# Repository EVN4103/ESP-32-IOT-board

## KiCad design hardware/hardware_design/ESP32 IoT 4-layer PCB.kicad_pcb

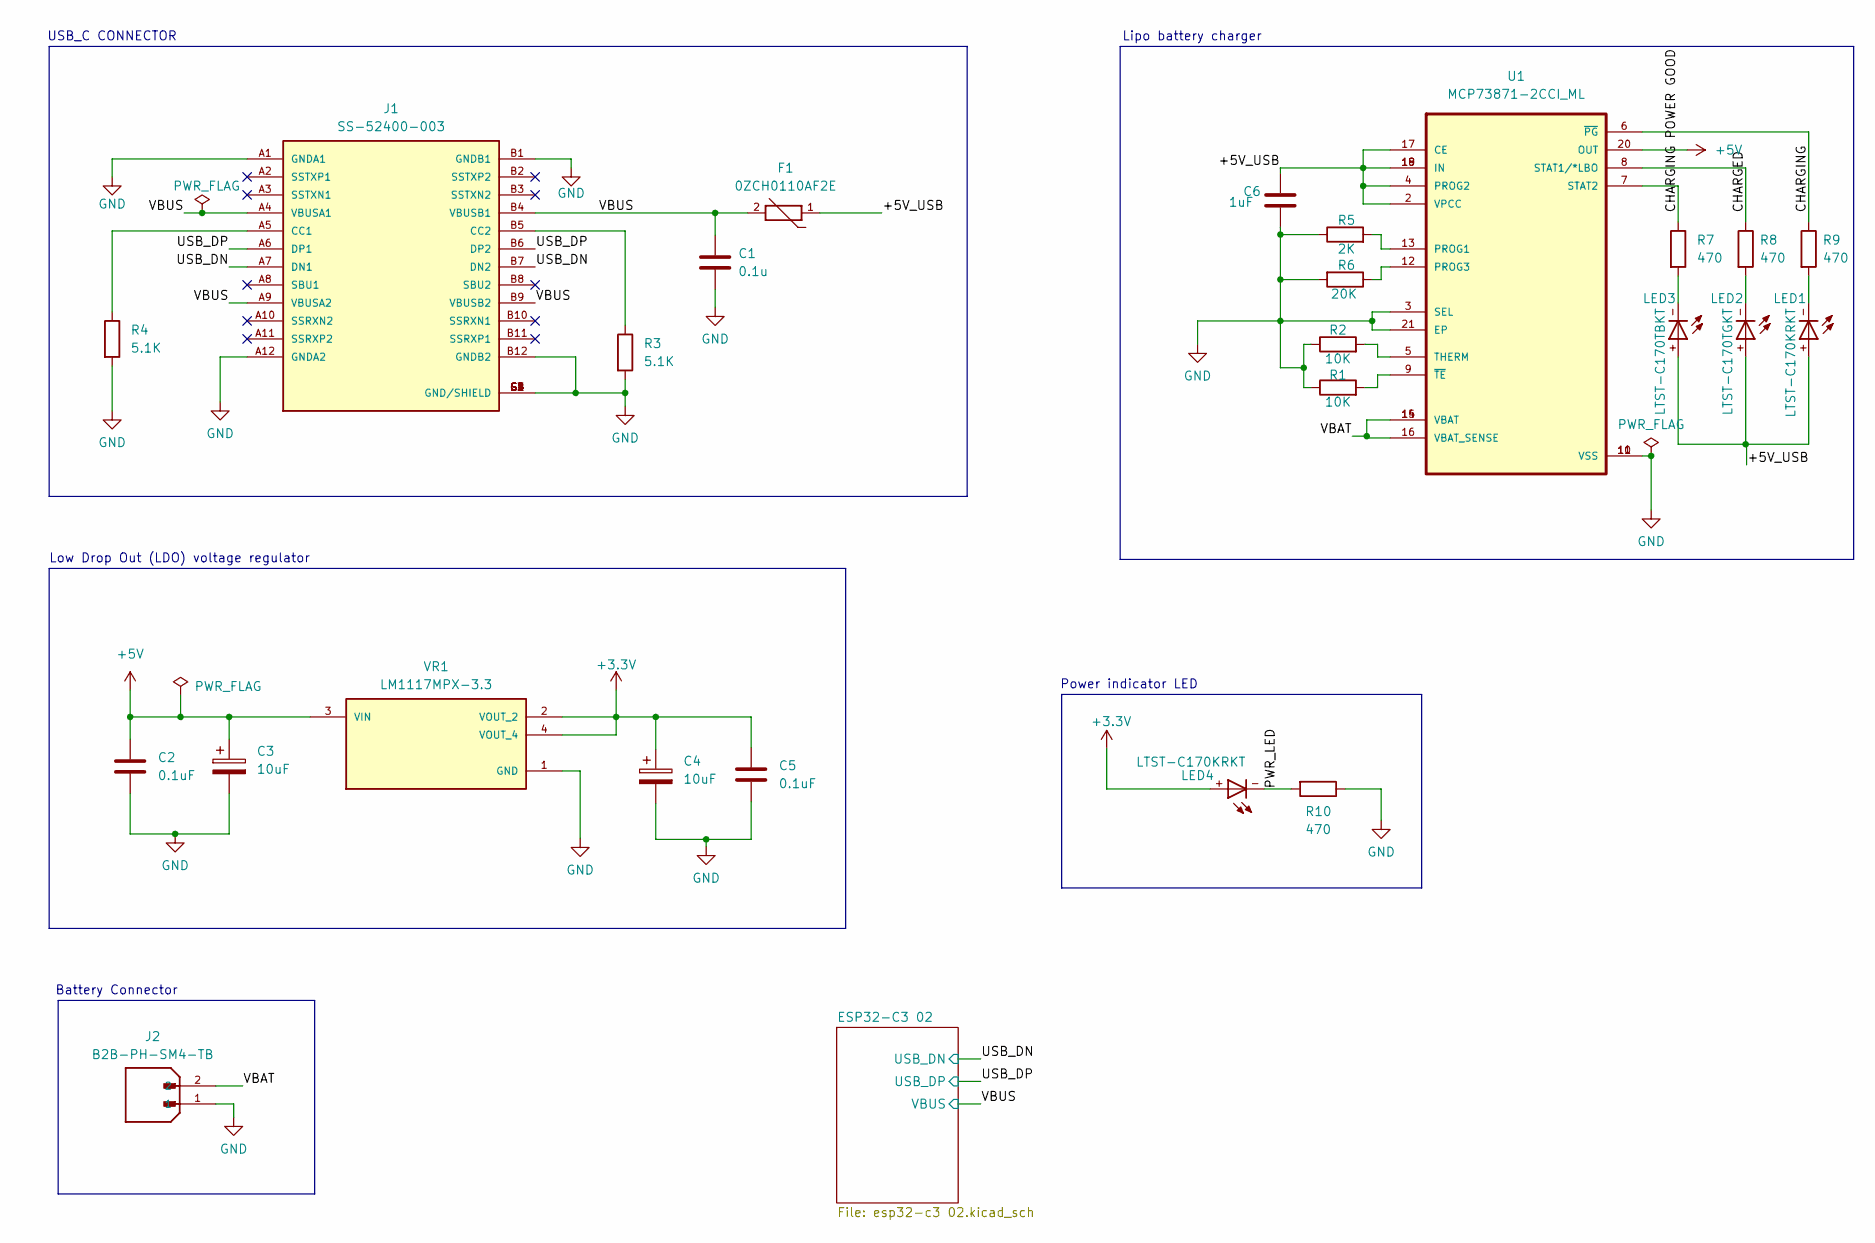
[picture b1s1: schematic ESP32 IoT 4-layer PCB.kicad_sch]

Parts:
C1: 0.1u; C_0805_2012Metric
C2, C5: 0.1uF; C_0805_2012Metric
C3, C4: 10uF; CP_EIA-3216-10_Kemet-I_HandSolder
C6: 1uF; C_0805_2012Metric
F1: 0ZCH0110AF2E; FUSC3225X100N; PARTREV Apr2023
J1: SS-52400-003; BELFUSE_SS-52400-003; PARTREV A0
J2: B2B-PH-SM4-TB; JST_B2B-PH-SM4-TB; PARTREV N/A
LED1, LED4: LTST-C170KRKT; DIOC200X125X110
LED2: LTST-C170TGKT; DIOC200X125X110
LED3: LTST-C170TBKT; DIOC200X125X110
R1, R2: 10K; R_0805_2012Metric
R3, R4: 5.1K; R_0805_2012Metric
R5: 2K; R_0805_2012Metric
R6: 20K; R_0805_2012Metric
R7, R8, R9, R10: 470; R_0805_2012Metric
U1: MCP73871-2CCI_ML; QFN50P400X400X100-21N
VR1: LM1117MPX-3.3; VREG_LM1117MPX-3.3; PARTREV O

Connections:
+5V: C2.1, C3.1, U1.1, U1.20 (OUT), VR1.3 (VIN)
/+5V_USB: C6.1, F1.1, U1.2 (VPCC), U1.4 (PROG2), U1.17 (CE), U1.18 (IN), U1.19 (IN)
/CHARGED: R8.1, U1.8 (STAT1/*LBO)
/CHARGING: R9.1, U1.6 (~PG)
/CHARGING POWER GOOD: R7.1, U1.7 (STAT2)
/PWR_LED: LED4.-, R10.2
/USB_DN: J1.A7 (DN1), J1.B7 (DN2); also elsewhere on the board
/USB_DP: J1.A6 (DP1), J1.B6 (DP2); also elsewhere on the board
/VBAT: J2.2, U1.14 (VBAT), U1.15 (VBAT), U1.16 (VBAT_SENSE)
/VBUS: C1.1, F1.2, J1.A4 (VBUSA1), J1.A9 (VBUSA2), J1.B4 (VBUSB1), J1.B9 (VBUSB2); also elsewhere on the board
GND: C1.2, C2.2, C3.2, C4.2, C5.2, C6.2, J1.A1 (GNDA1), J1.A12 (GNDA2), J1.B1 (GNDB1), J1.B12 (GNDB2), J1.G1 (GND/SHIELD), J1.G2 (GND/SHIELD), J1.G3 (GND/SHIELD), J1.G4 (GND/SHIELD), J1.S1 (GND/SHIELD), J1.S2 (GND/SHIELD), J1.S3 (GND/SHIELD), J1.S4 (GND/SHIELD), J2.1, R1.1, R2.1, R3.2, R4.2, R5.1, R6.2, R10.1, U1.3 (SEL), U1.10 (VSS), U1.11 (VSS), U1.21 (EP), VR1.1 (GND); also elsewhere on the board
unnamed: J1.A5 (CC1), R4.1
unnamed: J1.B5 (CC2), R3.1
unnamed: LED1.+, LED2.+, LED3.+
unnamed: LED1.-, R9.2
unnamed: LED2.-, R8.2
unnamed: LED3.-, R7.2
unnamed: R5.2, U1.13 (PROG1)
unnamed: R6.1, U1.12 (PROG3)
unnamed: R2.2, U1.5 (THERM)
unnamed: R1.2, U1.9 (~TE)

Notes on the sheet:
Power indicator LED
Battery Connector
Low Drop Out (LDO) voltage regulator
Lipo battery charger
USB_C CONNECTOR

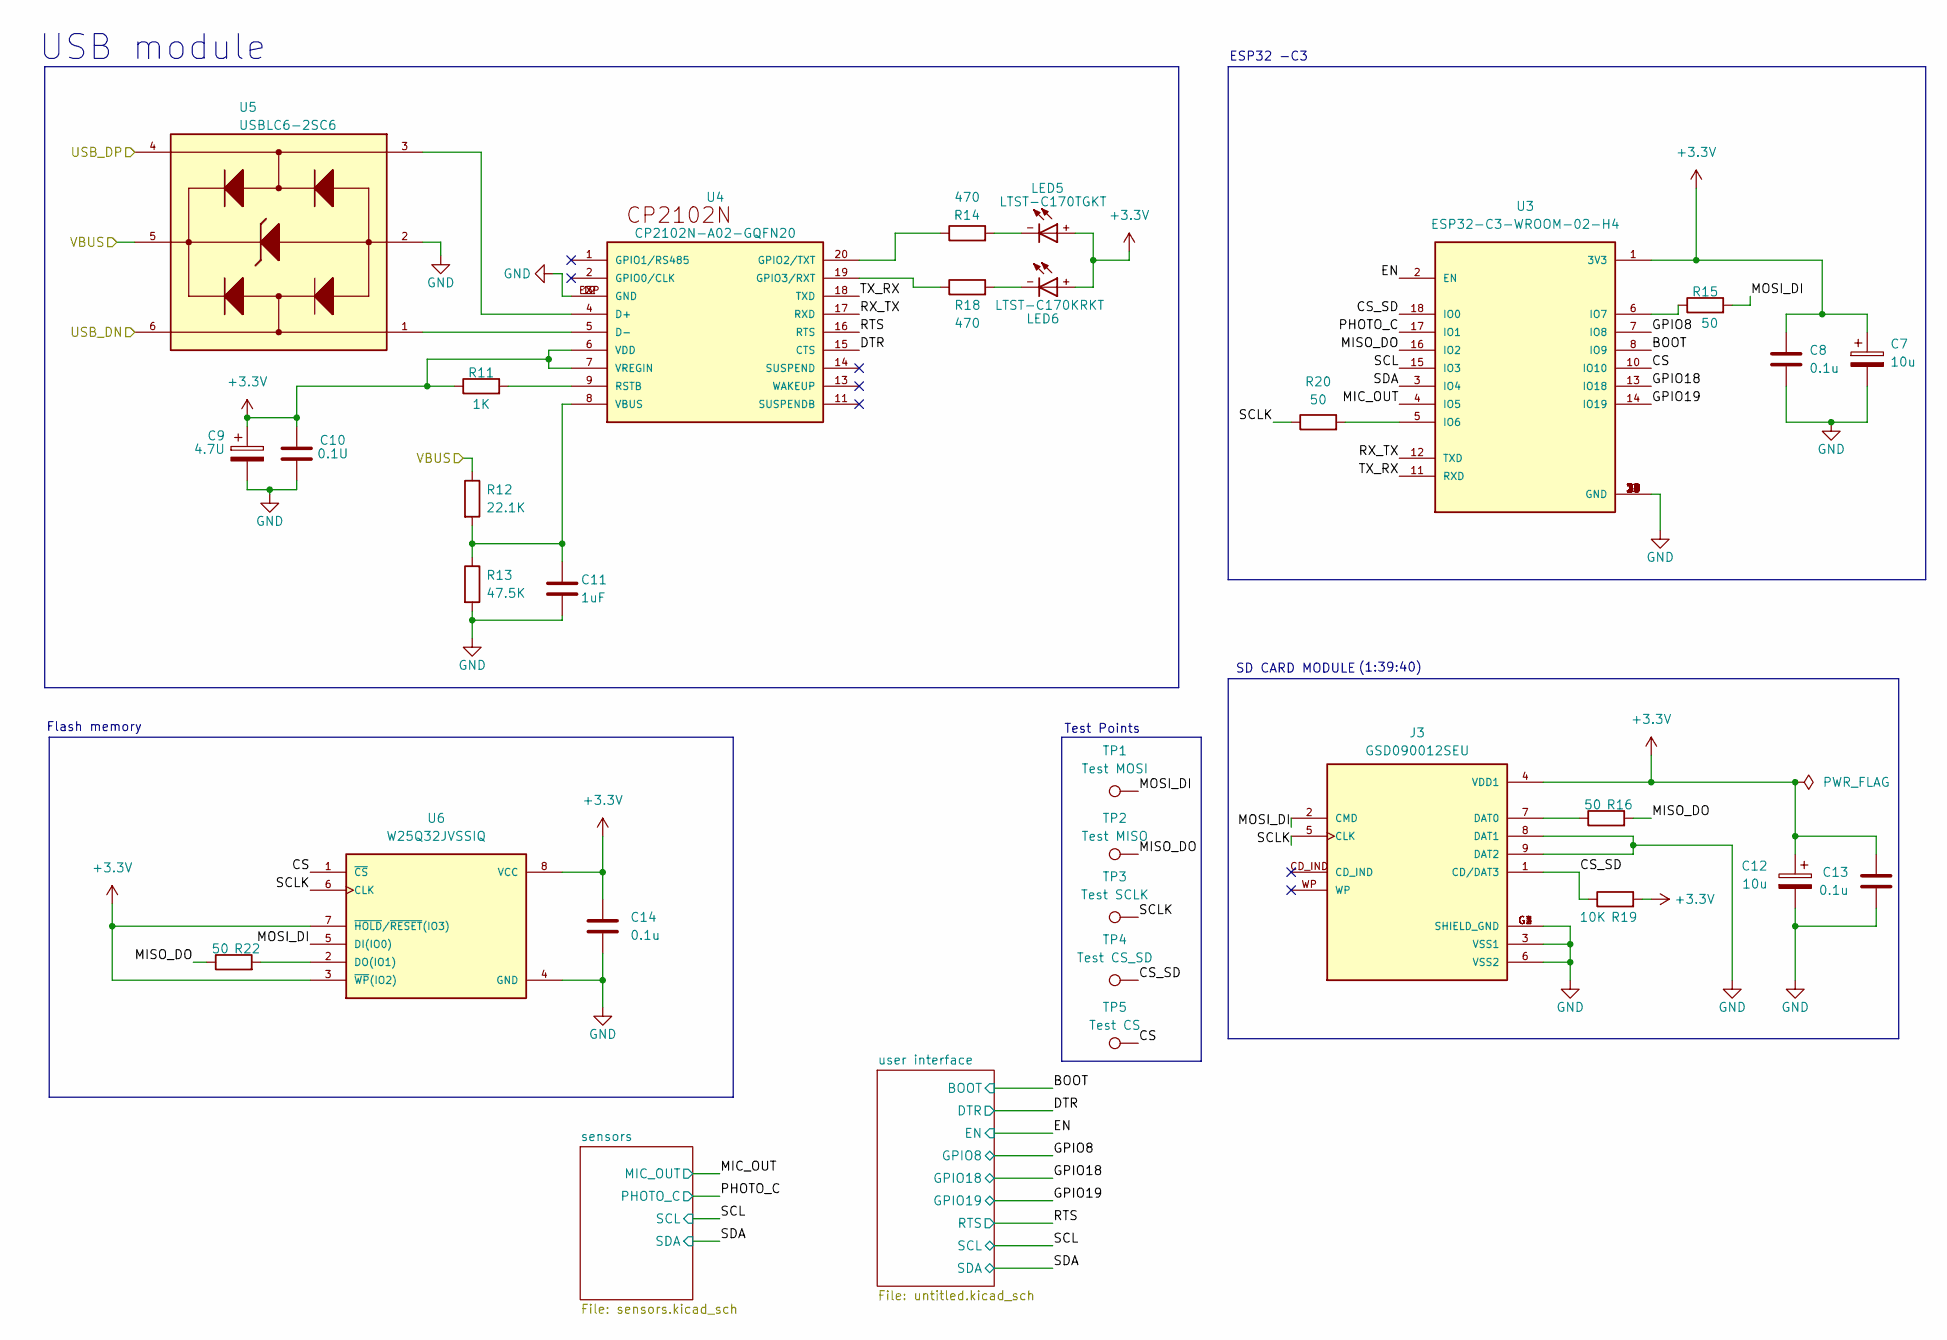
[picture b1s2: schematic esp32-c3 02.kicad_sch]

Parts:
C7, C12: 10u; CP_EIA-3216-10_Kemet-I_HandSolder
C8, C13, C14: 0.1u; C_0805_2012Metric
C9: 4.7U; CP_EIA-3216-10_Kemet-I_HandSolder
C10: 0.1U; C_0805_2012Metric
C11: 1uF; C_0805_2012Metric
J3: GSD090012SEU; AMPHENOL_GSD090012SEU; PARTREV E
LED5: LTST-C170TGKT; DIOC200X125X110
LED6: LTST-C170KRKT; DIOC200X125X110
R11: 1K; R_0805_2012Metric
R12: 22.1K; R_0805_2012Metric
R13: 47.5K; R_0805_2012Metric
R14, R18: 470; R_0805_2012Metric
R15, R16, R20, R22: 50; R_0805_2012Metric
R19: 10K; R_0805_2012Metric
TP1: Test MOSI; TestPoint_Pad_D1.0mm
TP2: Test MISO; TestPoint_Pad_D1.0mm
TP3: Test SCLK; TestPoint_Pad_D1.0mm
TP4: Test CS_SD; TestPoint_Pad_D1.0mm
TP5: Test CS; TestPoint_Pad_D1.0mm
U3: ESP32-C3-WROOM-02-H4; MODULE_ESP32-C3-WROOM-02-H4
U4: CP2102N-A02-GQFN20; WFQFN-20
U5: USBLC6-2SC6; SOT95P280X145-6N
U6: W25Q32JVSSIQ; SOIC127P790X216-8N; M_PART_NUMBER W25QXX

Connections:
/ESP32-C3 02/BOOT: U3.8 (IO9); also elsewhere on the board
/ESP32-C3 02/CS: TP5.1 (1_1), U3.10 (IO10), U6.1 (~CS)
/ESP32-C3 02/CS_SD: J3.1 (CD/DAT3), R19.1, TP4.1 (1_1), U3.18 (IO0)
/ESP32-C3 02/DTR: U4.15 (CTS); also elsewhere on the board
/ESP32-C3 02/EN: U3.2 (EN); also elsewhere on the board
/ESP32-C3 02/GPIO8: U3.7 (IO8); also elsewhere on the board
/ESP32-C3 02/GPIO18: U3.13 (IO18); also elsewhere on the board
/ESP32-C3 02/GPIO19: U3.14 (IO19); also elsewhere on the board
/ESP32-C3 02/MIC_OUT: U3.4 (IO5); also elsewhere on the board
/ESP32-C3 02/MISO_DO: R16.2, R22.1, TP2.1 (1_1), U3.16 (IO2)
/ESP32-C3 02/MOSI_DI: J3.2 (CMD), R15.2, TP1.1 (1_1), U6.5 (DI(IO0))
/ESP32-C3 02/PHOTO_C: U3.17 (IO1); also elsewhere on the board
/ESP32-C3 02/RTS: U4.16 (RTS); also elsewhere on the board
/ESP32-C3 02/RX_TX: U3.12 (TXD), U4.17 (RXD)
/ESP32-C3 02/SCL: U3.15 (IO3); also elsewhere on the board
/ESP32-C3 02/SCLK: J3.5 (CLK), R20.1, TP3.1 (1_1), U6.6 (CLK)
/ESP32-C3 02/SDA: U3.3 (IO4); also elsewhere on the board
/ESP32-C3 02/TX_RX: U3.11 (RXD), U4.18 (TXD)
/USB_DN: U5.6; also elsewhere on the board
/USB_DP: U5.4; also elsewhere on the board
/VBUS: R12.1, U5.5; also elsewhere on the board
GND: C7.2, C8.2, C9.2, C10.1, C11.2, C12.2, C13.2, C14.2, J3.3 (VSS1), J3.6 (VSS2), J3.8 (DAT1), J3.9 (DAT2), J3.G1 (SHIELD_GND), J3.G2 (SHIELD_GND), J3.G3 (SHIELD_GND), J3.G4 (SHIELD_GND), R13.2, U3.9 (GND), U3.19 (GND), U3.20 (GND), U3.21 (GND), U3.22 (GND), U3.23 (GND), U3.24 (GND), U3.25 (GND), U3.26 (GND), U3.27 (GND), U3.28 (GND), U3.29 (GND), U3.30 (GND), U3.31 (GND), U3.32 (GND), U3.33 (GND), U3.34 (GND), U3.35 (GND), U3.36 (GND), U3.37 (GND), U3.38 (GND), U3.39 (GND), U4.3 (GND), U4.12 (GND), U4.EXP (GND), U5.2, U6.4 (GND); also elsewhere on the board
unnamed: J3.7 (DAT0), R16.1
unnamed: LED5.-, R14.2
unnamed: LED6.-, R18.2
unnamed: R20.2, U3.5 (IO6)
unnamed: R15.1, U3.6 (IO7)
unnamed: U4.4 (D+), U5.3
unnamed: U4.5 (D-), U5.1
unnamed: R14.1, U4.20 (GPIO2/TXT)
unnamed: R18.1, U4.19 (GPIO3/RXT)
unnamed: R11.2, U4.9 (RSTB)
unnamed: R22.2, U6.2 (DO(IO1))

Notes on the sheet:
ESP32 -C3
SD CARD MODULE
Test Points
(1:39:40)
Flash memory
USB module

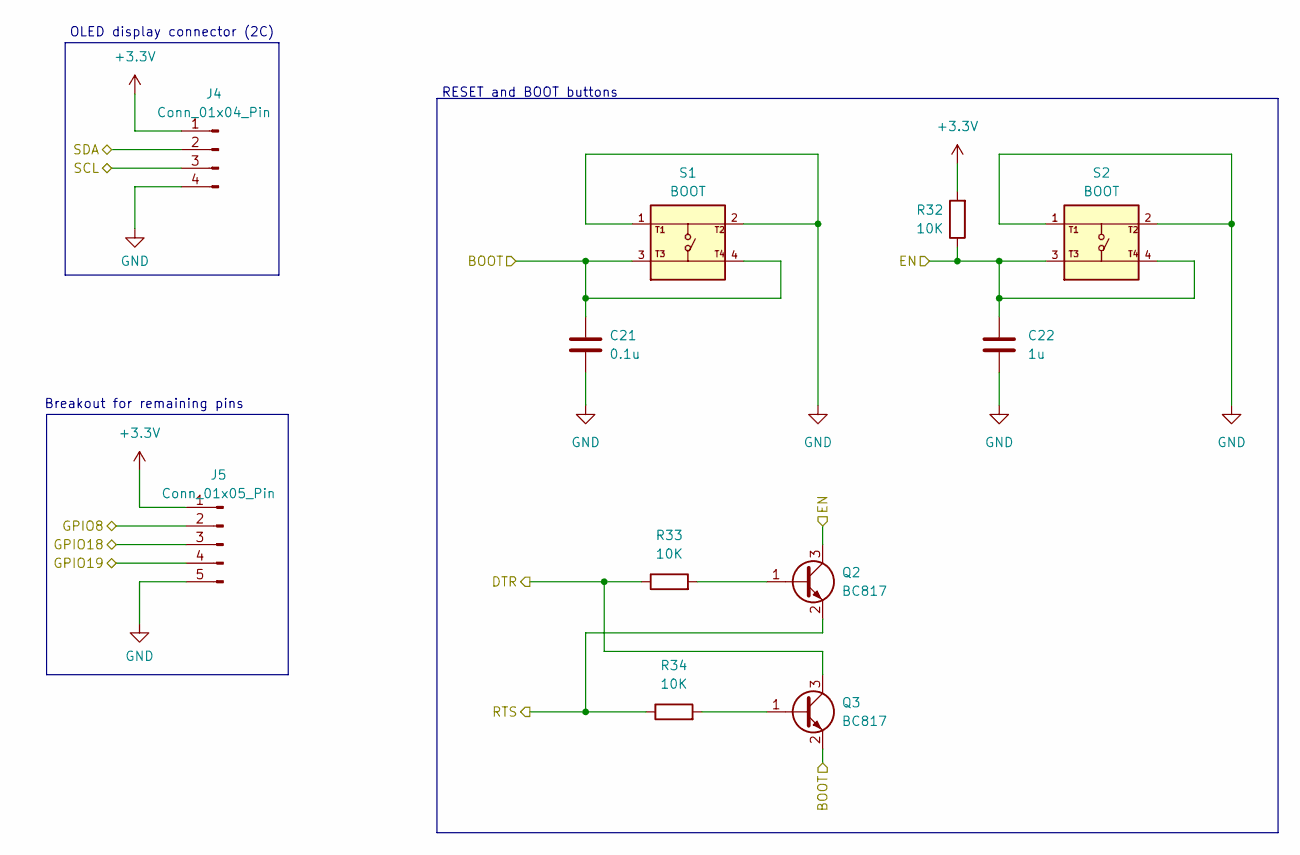
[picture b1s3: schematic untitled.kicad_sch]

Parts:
C21: 0.1u; C_0805_2012Metric
C22: 1u; C_0805_2012Metric
J4: Conn_01x04_Pin; PinHeader_1x04_P2.54mm_Vertical
J5: Conn_01x05_Pin; PinHeader_1x05_P2.54mm_Vertical
Q2, Q3: BC817; SOT-23
R32, R33, R34: 10K; R_0805_2012Metric
S1, S2: BOOT; SW_USLPT2819DT2TR; PARTREV P

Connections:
/ESP32-C3 02/BOOT: C21.1, Q3.2 (E), S1.3, S1.4; also elsewhere on the board
/ESP32-C3 02/DTR: Q3.3 (C), R33.1; also elsewhere on the board
/ESP32-C3 02/EN: C22.1, Q2.3 (C), R32.1, S2.3, S2.4; also elsewhere on the board
/ESP32-C3 02/GPIO8: J5.2; also elsewhere on the board
/ESP32-C3 02/GPIO18: J5.3; also elsewhere on the board
/ESP32-C3 02/GPIO19: J5.4; also elsewhere on the board
/ESP32-C3 02/RTS: Q2.2 (E), R34.1; also elsewhere on the board
/ESP32-C3 02/SCL: J4.3; also elsewhere on the board
/ESP32-C3 02/SDA: J4.2; also elsewhere on the board
GND: C21.2, C22.2, J4.4, J5.5, S1.1, S1.2, S2.1, S2.2; also elsewhere on the board
unnamed: Q2.1 (B), R33.2
unnamed: Q3.1 (B), R34.2

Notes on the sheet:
RESET and BOOT buttons
Breakout for remaining pins
OLED display connector (2C)

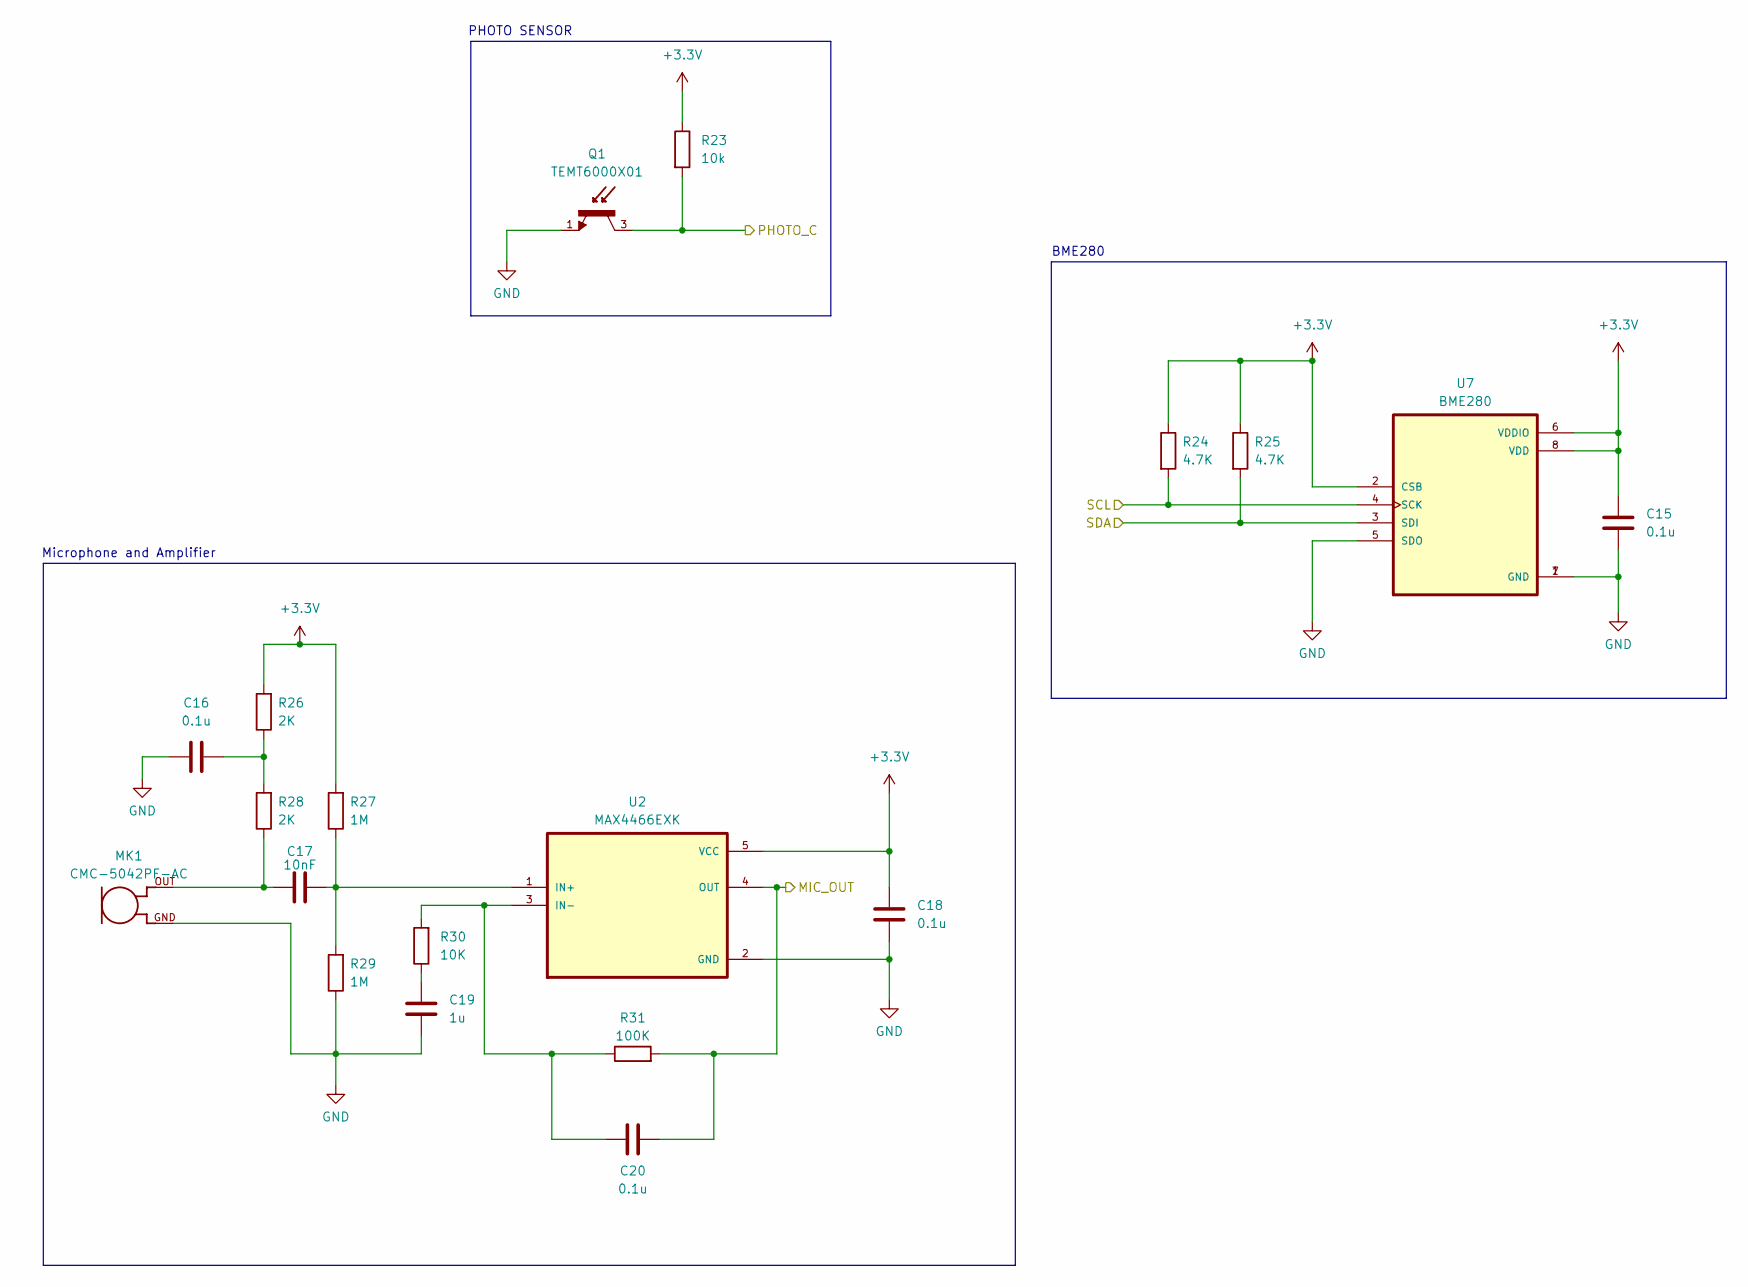
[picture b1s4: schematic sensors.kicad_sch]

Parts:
C15, C16, C18, C20: 0.1u; C_0805_2012Metric
C17: 10nF; C_0805_2012Metric
C19: 1u; C_0805_2012Metric
MK1: CMC-5042PF-AC; CUI_CMC-5042PF-AC
Q1: TEMT6000X01; TRANS_TEMT6000X01; PARTREV 1.9
R23: 10k; R_0805_2012Metric
R24, R25: 4.7K; R_0805_2012Metric
R26, R28: 2K; R_0805_2012Metric
R27, R29: 1M; R_0805_2012Metric
R30: 10K; R_0805_2012Metric
R31: 100K; R_0805_2012Metric
U2: MAX4466EXK; SOT65P210X110-5N
U7: BME280; PSON65P250X250X100-8N

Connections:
/ESP32-C3 02/MIC_OUT: C20.2, R31.2, U2.4 (OUT); also elsewhere on the board
/ESP32-C3 02/PHOTO_C: Q1.3, R23.2; also elsewhere on the board
/ESP32-C3 02/SCL: R24.2, U7.4 (SCK); also elsewhere on the board
/ESP32-C3 02/SDA: R25.2, U7.3 (SDI); also elsewhere on the board
GND: C15.2, C16.1, C18.2, C19.2, MK1.GND, Q1.1, R29.1, U2.2 (GND), U7.1 (GND), U7.5 (SDO), U7.7 (GND); also elsewhere on the board
unnamed: C16.2, R26.1, R28.2
unnamed: C17.1, MK1.OUT, R28.1
unnamed: C19.1, R30.1
unnamed: C17.2, R27.1, R29.2, U2.1 (IN+)
unnamed: C20.1, R30.2, R31.1, U2.3 (IN-)

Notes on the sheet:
BME280
PHOTO SENSOR
Microphone and Amplifier

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
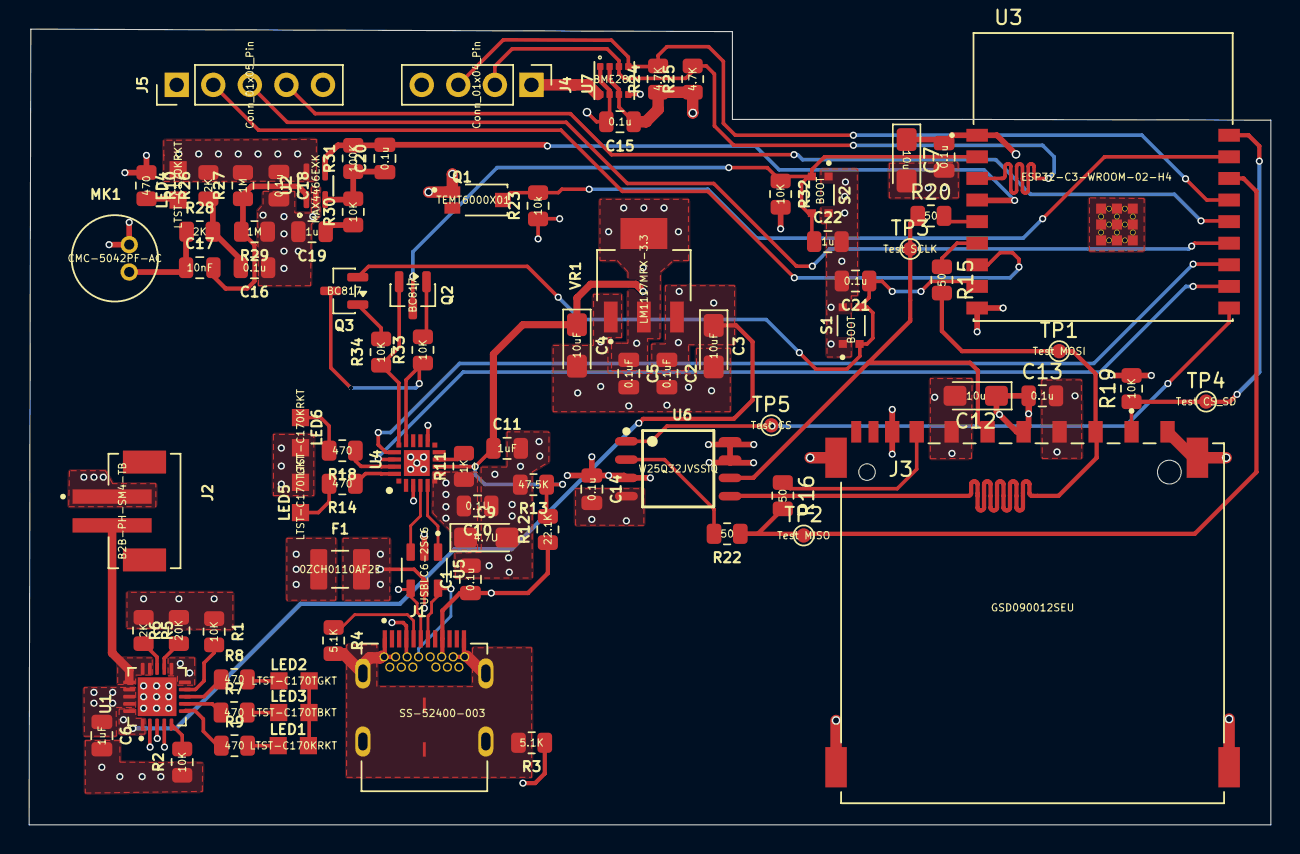
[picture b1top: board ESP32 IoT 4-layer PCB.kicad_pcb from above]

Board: 4 copper layers, 86.2 x 55.3 mm, 85 parts (0 on the bottom side), 59 nets.

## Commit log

2026-04-09 schematics 100% completed
2026-04-18 pcb layout completed
2026-04-18 Remove .history from submodule
